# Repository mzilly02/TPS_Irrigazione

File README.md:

# TPS_Irrigazione
Sistema di irrigazione con 5 aree programmabili e gestione attivazione tramite sensori di umidità industriali e sistema RTC DS1307 (Timer I2C).

Il progetto si basa su un Arduino Uno R3 incluso in un PCB custom (dimensioni nel file .brd), il tutto montato in un case stampato in 3d su una barra DIN (barra 35mm per montaggio PLC). 

L’intero sistema è inserito in una scatola di distribuzione impermeabile per permettere all’utente di installare il sistema di controllo all’esterno.

Il sistema è alimentato tramite un alimentatore per PLC a 12V / 2,5A MAX con doppia uscita 12V (Arduino e elettrovalvole).

Controllo del sistema tramite 4 tasti: SET, SW, UP e DOWN.

visualizzazione dati usando i display 7 segmenti in connessione I2C.

I sensori di umidità industriali sono attivati quando è presente una programmazione, per permettere un risparmio d'acqua all'utente.

L'attivazione dell'irrigazione è attuata tramite 5 elettrovalvole a 12v di tipo NC, controllate da 5 relè a stato solido.

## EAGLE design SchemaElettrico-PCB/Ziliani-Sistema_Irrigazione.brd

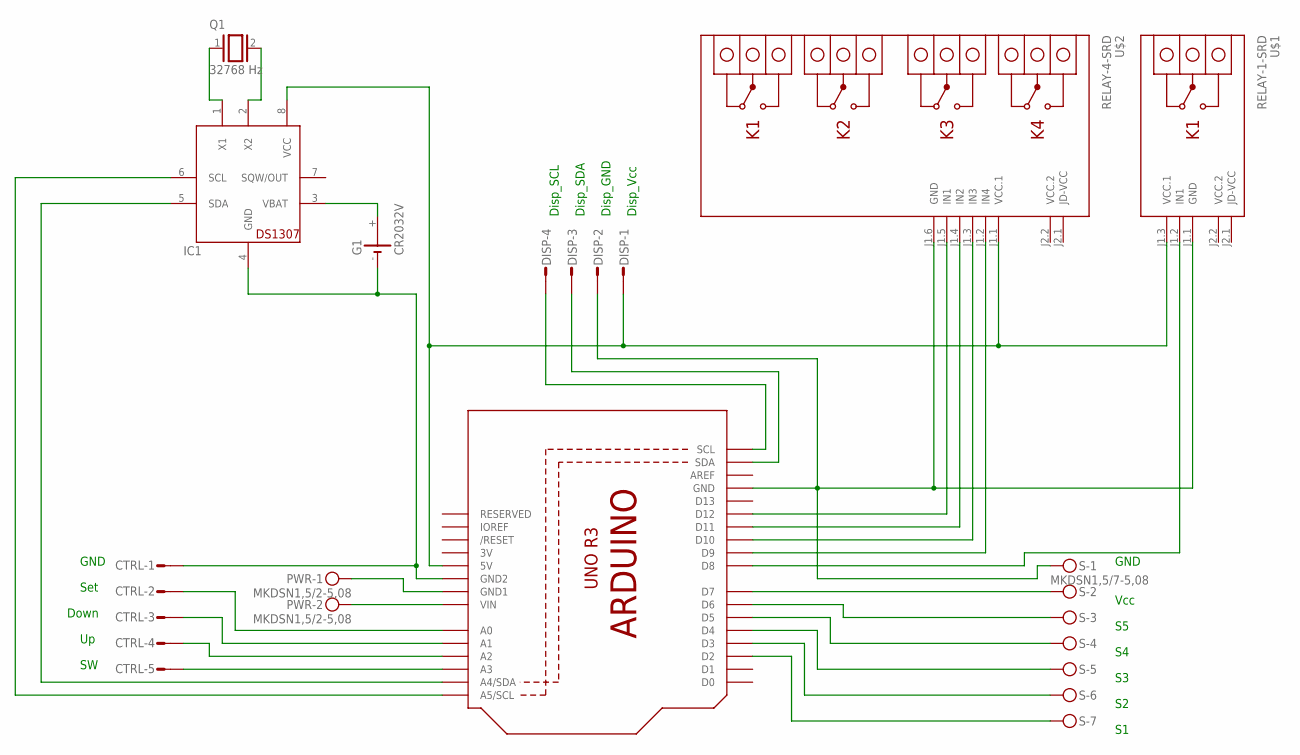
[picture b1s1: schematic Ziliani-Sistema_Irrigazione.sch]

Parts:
CTRL: L05P
DISP: L04P
G1: CR2032V
IC1: DS1307; DIL08
PWR: MKDSN1,5/2-5,08
Q1: 32768 Hz; QS
S: MKDSN1,5/7-5,08
U1: ARDUINOR3-DIMENSION; ARDUINOR3
U$1: RELAY-1-SRD
U$2: RELAY-4-SRD

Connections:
3V: U1.3V
GND: PWR.1, U1.GND1
unnamed: G1.+, IC1.3 (VBAT)
unnamed: DISP.4, U1.SCL
unnamed: IC1.2 (X2), Q1.2
unnamed: IC1.1 (X1), Q1.1
unnamed: CTRL.2, U1.A0
unnamed: IC1.5 (SDA), U1.A4 (A4/SDA)
unnamed: IC1.6 (SCL), U1.A5 (A5/SCL)
unnamed: CTRL.1, G1.-, IC1.4 (GND), U1.GND2
unnamed: CTRL.3, U1.A1
unnamed: CTRL.4, U1.A2
unnamed: CTRL.5, U1.A3
unnamed: PWR.2, U1.VIN
unnamed: DISP.1, IC1.8 (VCC), U1.5V, U$1.J1.3 (VCC.1), U$2.J1.1 (VCC.1)
unnamed: U1.D11, U$2.J1.4 (IN2)
unnamed: DISP.2, S.1, U1.GND, U$1.J1.1 (GND), U$2.J1.6 (GND)
unnamed: S.7, U1.D2
unnamed: S.6, U1.D3
unnamed: S.5, U1.D4
unnamed: S.4, U1.D5
unnamed: S.3, U1.D6
unnamed: S.2, U1.D7
unnamed: DISP.3, U1.SDA
unnamed: U1.D8, U$1.J1.2 (IN1)
unnamed: U1.D10, U$2.J1.3 (IN3)
unnamed: U1.D9, U$2.J1.2 (IN4)
unnamed: U1.D12, U$2.J1.5 (IN1)
VCC.2: U$1.J2.2 (VCC.2), U$2.J2.2 (VCC.2)

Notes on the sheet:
GND
Down
Set
Vcc
Disp_Vcc
Disp_GND
Disp_SDA
Disp_SCL

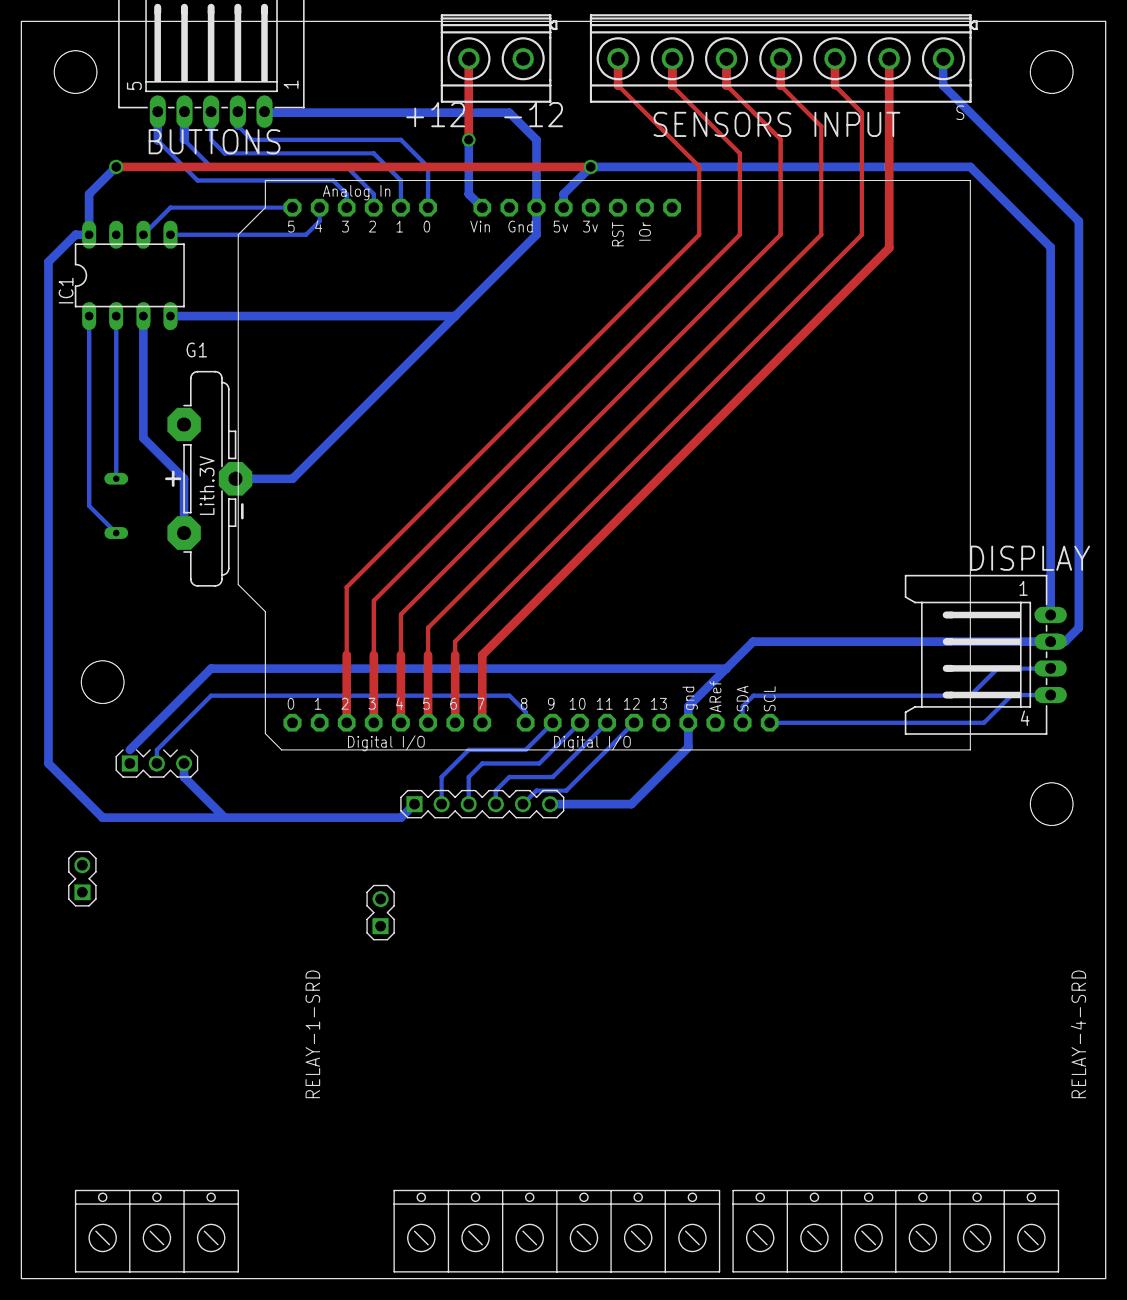
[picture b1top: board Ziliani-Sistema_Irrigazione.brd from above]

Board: 2 copper layers, 101.6 x 117.8 mm, 10 parts (1 on the bottom side), 28 nets.

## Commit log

2020-05-26 Add files via upload
    Versione iniziale

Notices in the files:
parts and their libraries:
diy-modules-PCB: Released under the Creative Commons Attribution 4.0 International License: http://creativecommons.org/licenses/by/4.0
